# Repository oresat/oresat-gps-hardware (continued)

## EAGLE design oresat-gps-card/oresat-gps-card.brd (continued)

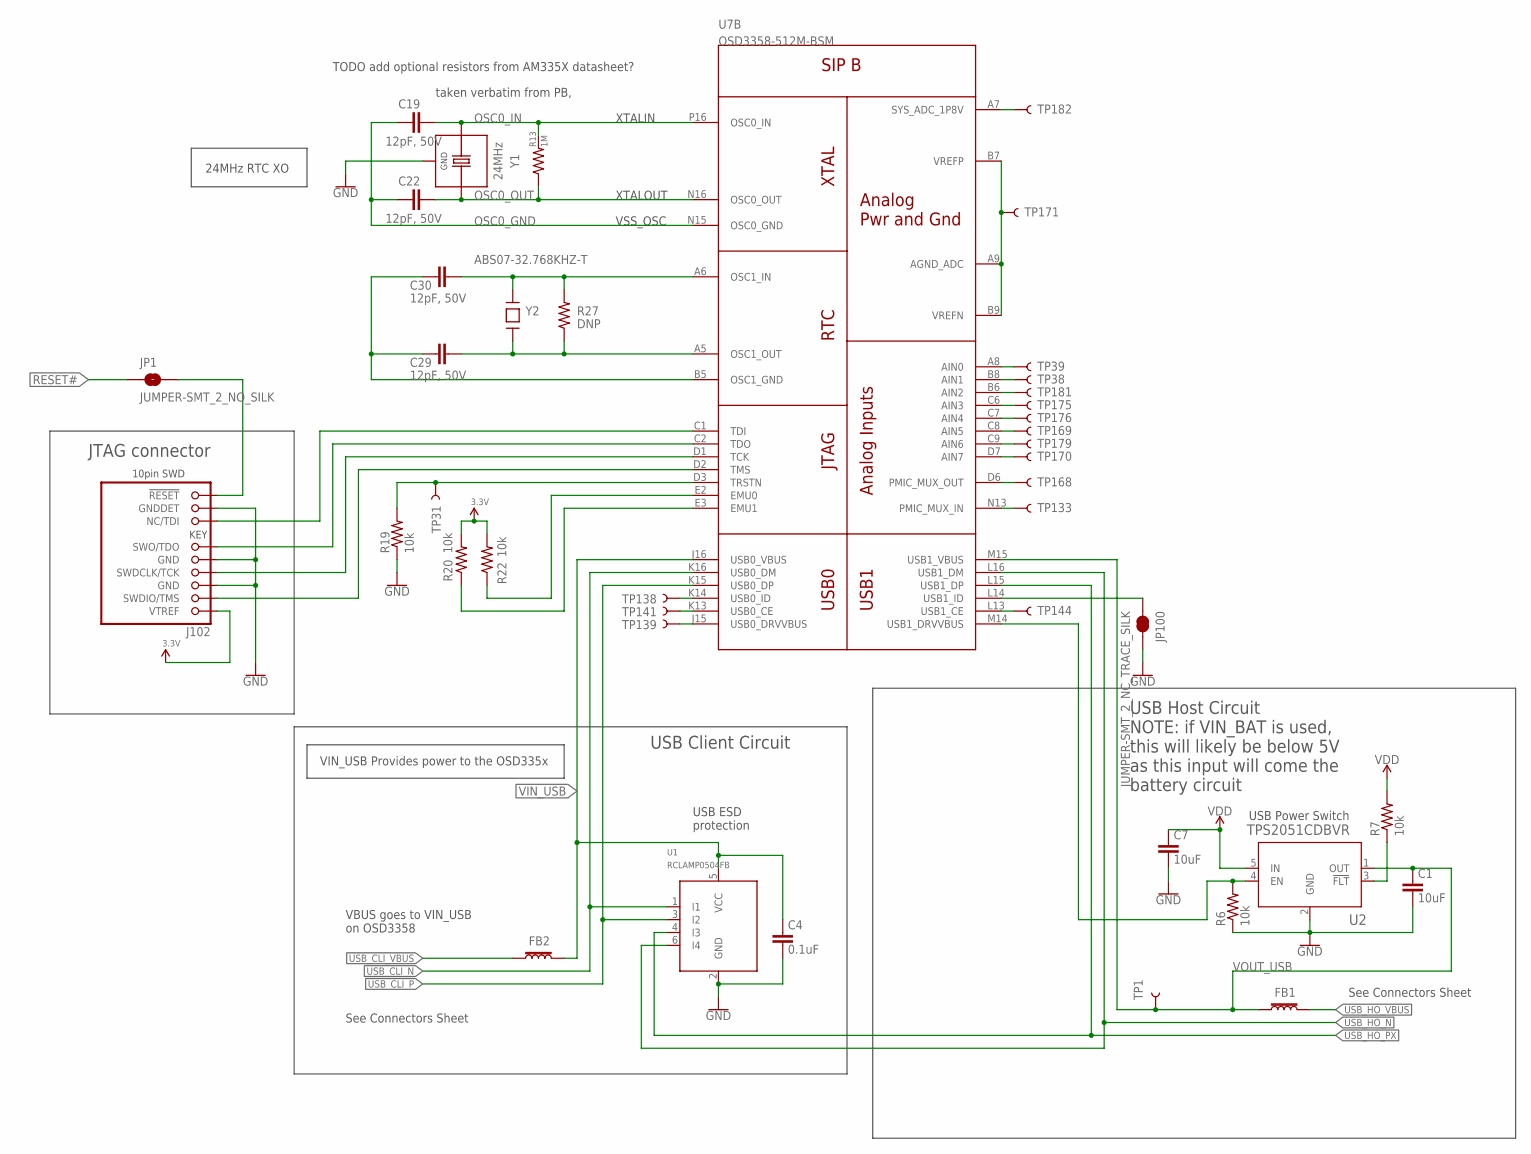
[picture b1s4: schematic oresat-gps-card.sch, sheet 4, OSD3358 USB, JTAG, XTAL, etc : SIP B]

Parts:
C1, C7: 10uF; .0805-B
C4: 0.1uF; .0603-A
C19, C22, C29, C30: 12pF, 50V; .0603-A
FB1, FB2: 30Ω/1.8A; 0603; MPN BLM18KG300JH1D
J102: FTSH-105-XX-X-DV-K; CON10_2X5_DUK_FTSH
JP1: JUMPER-SMT_2_NO_SILK; SMT-JUMPER_2_NO_SILK
JP100: JUMPER-SMT_2_NC_TRACE_SILK; SMT-JUMPER_2_NC_TRACE_SILK
R6, R7, R19, R20, R22: 10k; .0603-A
R13: 1M; .0603-A
R27: DNP; .0603-A
TP1, TP31, TP38, TP39, TP133, TP138, TP139, TP141, TP144, TP168, TP169, TP170, TP171, TP175, TP176, TP179, TP181, TP182: TEST-POINT3X4; PAD.03X.04
U1: RCLAMP0504FB; SC70-6
U2: TPS2051CDBVR; DBV5
U7: OSD3358-512M-BSM; OSD335X-BGA-256
Y1: 24MHz; 5X3.2-4SMD
Y2: ABS07-32.768KHZ-T; CRYSTAL_3.2X1.5

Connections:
3.3V: J102.1 (VTREF), R20.2, R22.2; also elsewhere on the board
GND: C1.2, C4.2, C7.2, J102.3 (GND), J102.5 (GND), J102.9 (GNDDET), JP100.2, R6.1, R19.1, U1.2 (GND), U2.2 (GND), Y1.2 (GND), Y1.4 (GND); also elsewhere on the board
unnamed: TP171.P$1, U7.A9 (AGND_ADC), U7.B7 (VREFP), U7.B9 (VREFN)
unnamed: TP170.P$1, U7.D7 (AIN7)
unnamed: TP179.P$1, U7.C9 (AIN6)
unnamed: TP169.P$1, U7.C8 (AIN5)
unnamed: TP176.P$1, U7.C7 (AIN4)
unnamed: TP175.P$1, U7.C6 (AIN3)
unnamed: TP181.P$1, U7.B6 (AIN2)
unnamed: TP38.P$1, U7.B8 (AIN1)
unnamed: TP39.P$1, U7.A8 (AIN0)
unnamed: TP141.P$1, U7.K13 (USB0_CE)
unnamed: TP139.P$1, U7.J15 (USB0_DRVVBUS)
unnamed: TP182.P$1, U7.A7 (SYS_ADC_1P8V)
unnamed: TP168.P$1, U7.D6 (PMIC_MUX_OUT)
unnamed: R20.1, U7.E3 (EMU1)
unnamed: TP144.P$1, U7.L13 (USB1_CE)
unnamed: R22.1, U7.E2 (EMU0)
unnamed: JP100.1, U7.L14 (USB1_ID)
unnamed: TP138.P$1, U7.K14 (USB0_ID)
unnamed: J102.10 (!RESET), JP1.2
unnamed: J102.6 (SWO/TDO), U7.C2 (TDO)
unnamed: J102.4 (SWDCLK/TCK), U7.D1 (TCK)
unnamed: J102.2 (SWDIO/TMS), U7.D2 (TMS)
unnamed: R6.2, U2.4 (EN), U7.M14 (USB1_DRVVBUS)
unnamed: R7.1, U2.3 (!FLT)
unnamed: J102.8 (NC/TDI), U7.C1 (TDI)
unnamed: R19.2, TP31.P$1, U7.D3 (TRSTN)
OSC0_GND: C19.1, C22.1, U7.N15 (OSC0_GND)
OSC0_IN: C19.2, R13.2, U7.P16 (OSC0_IN), Y1.1 (X1)
OSC0_OUT: C22.2, R13.1, U7.N16 (OSC0_OUT), Y1.3 (X2)
OSC1_GND1: C29.2, C30.2, U7.B5 (OSC1_GND)
OSC1_IN1: C30.1, R27.2, U7.A6 (OSC1_IN), Y2.P$2
OSC1_OUT1: C29.1, R27.1, U7.A5 (OSC1_OUT), Y2.P$1
PMIC_MUX_IN: TP133.P$1, U7.N13 (PMIC_MUX_IN)
RESET#: JP1.1; also elsewhere on the board
USB_CLI_N: U1.1 (I1), U7.K16 (USB0_DM); also elsewhere on the board
USB_CLI_P: U1.3 (I2), U7.K15 (USB0_DP); also elsewhere on the board
USB_CLI_VBUS: FB2.1; also elsewhere on the board
USB_HO_N: U1.6 (I4), U7.L16 (USB1_DM); also elsewhere on the board
USB_HO_PX: U1.4 (I3), U7.L15 (USB1_DP); also elsewhere on the board
USB_HO_VBUS: FB1.2; also elsewhere on the board
VDD: C7.1, R7.2, U2.5 (IN); also elsewhere on the board
VIN_USB: C4.1, FB2.2, U1.5 (VCC), U7.J16 (USB0_VBUS); also elsewhere on the board
VOUT_USB: C1.1, FB1.1, TP1.P$1, U2.1 (OUT), U7.M15 (USB1_VBUS)

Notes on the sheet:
taken verbatim from PB,
VBUS goes to VIN_USB on OSD3358
USB ESD protection
USB Host Circuit NOTE: if VIN_BAT is used, this will likely be below 5V as this input will come the battery circuit
USB Power Switch
JTAG connector
USB Client Circuit
24MHz RTC XO
See Connectors Sheet
TODO add optional resistors from AM335X datasheet?
XTALIN
XTALOUT
VSS_OSC
VIN_USB Provides power to the OSD335x

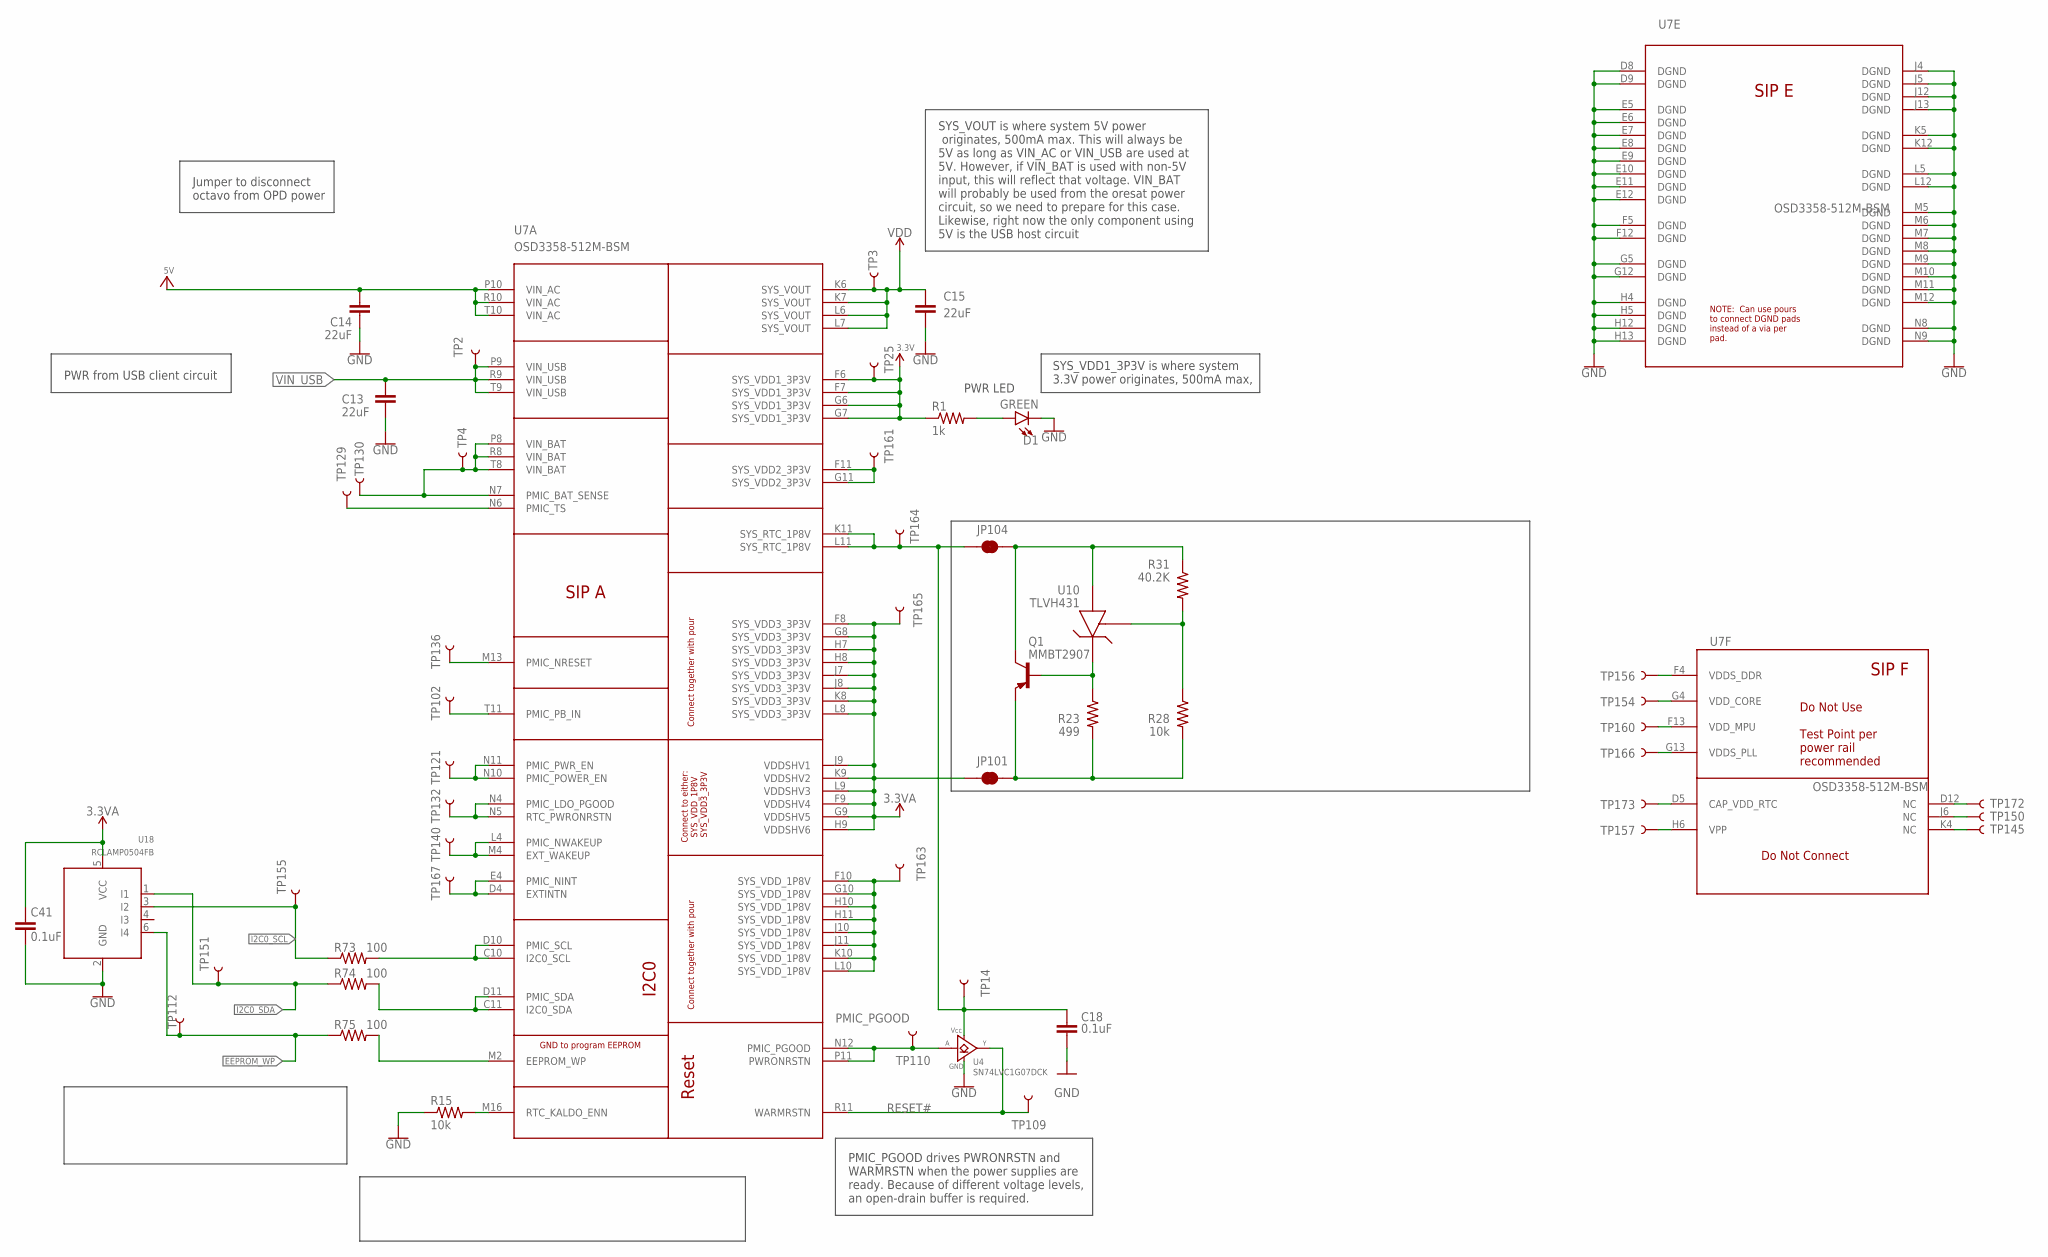
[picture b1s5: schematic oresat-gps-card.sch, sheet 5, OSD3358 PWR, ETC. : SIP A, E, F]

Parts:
C13, C14, C15: 22uF; C1210
C18, C41: 0.1uF; .0603-A
D1: GREEN; LED-0603
JP101, JP104: JUMPER-SMT_2_NC_TRACE_SILK; SMT-JUMPER_2_NC_TRACE_SILK
Q1: MMBT2907; SOT23-BEC
R1: 1k; .0603-A
R15, R28: 10k; .0603-A
R23: 499; .0603-A
R31: 40.2K; .0603-A
R73, R74, R75: 100; .0603-A
TP2, TP3, TP4, TP14, TP25, TP102, TP109, TP110, TP112, TP121, TP129, TP130, TP132, TP136, TP140, TP145, TP150, TP151, TP154, TP155, TP156, TP157, TP160, TP161, TP163, TP164, TP165, TP166, TP167, TP172, TP173: TEST-POINT3X4; PAD.03X.04
U4: SN74LVC1G07DCK; C70(TI-DCK)
U7: OSD3358-512M-BSM; OSD335X-BGA-256
U10: TLVH431; SOT23-3
U18: RCLAMP0504FB; SC70-6

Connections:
3.3V: R1.1, TP25.P$1, U7.F6 (SYS_VDD1_3P3V), U7.F7 (SYS_VDD1_3P3V), U7.G6 (SYS_VDD1_3P3V), U7.G7 (SYS_VDD1_3P3V); also elsewhere on the board
3.3VA: C41.1, JP101.1, TP165.P$1, U7.F8 (SYS_VDD3_3P3V), U7.F9 (VDDSHV4), U7.G8 (SYS_VDD3_3P3V), U7.G9 (VDDSHV5), U7.H7 (SYS_VDD3_3P3V), U7.H8 (SYS_VDD3_3P3V), U7.H9 (VDDSHV6), U7.J7 (SYS_VDD3_3P3V), U7.J8 (SYS_VDD3_3P3V), U7.J9 (VDDSHV1), U7.K8 (SYS_VDD3_3P3V), U7.K9 (VDDSHV2), U7.L8 (SYS_VDD3_3P3V), U7.L9 (VDDSHV3), U18.5 (VCC)
5V: C14.1, U7.P10 (VIN_AC), U7.R10 (VIN_AC), U7.T10 (VIN_AC); also elsewhere on the board
EEPROM_WP: R75.1, TP112.P$1, U18.6 (I4); also elsewhere on the board
GND: C13.2, C14.2, C15.2, C18.2, C41.2, D1.C, R15.1, U4.3 (GND), U7.D8 (DGND), U7.D9 (DGND), U7.E5 (DGND), U7.E6 (DGND), U7.E7 (DGND), U7.E8 (DGND), U7.E9 (DGND), U7.E10 (DGND), U7.E11 (DGND), U7.E12 (DGND), U7.F5 (DGND), U7.F12 (DGND), U7.G5 (DGND), U7.G12 (DGND), U7.H4 (DGND), U7.H5 (DGND), U7.H12 (DGND), U7.H13 (DGND), U7.J4 (DGND), U7.J5 (DGND), U7.J12 (DGND), U7.J13 (DGND), U7.K5 (DGND), U7.K12 (DGND), U7.L5 (DGND), U7.L12 (DGND), U7.M5 (DGND), U7.M6 (DGND), U7.M7 (DGND), U7.M8 (DGND), U7.M9 (DGND), U7.M10 (DGND), U7.M11 (DGND), U7.M12 (DGND), U7.N8 (DGND), U7.N9 (DGND), U18.2 (GND); also elsewhere on the board
I2C0_SCL: R73.1, TP155.P$1, U18.3 (I2); also elsewhere on the board
I2C0_SDA: R74.1, TP151.P$1, U18.1 (I1); also elsewhere on the board
unnamed: JP101.2, Q1.E, R23.2, R28.2
unnamed: R28.1, R31.2, U10.1 (REF)
unnamed: Q1.B, R23.1, U10.2 (CATHODE)
unnamed: TP172.P$1, U7.D12 (NC)
unnamed: TP150.P$1, U7.J6 (NC)
unnamed: TP145.P$1, U7.K4 (NC)
unnamed: TP157.P$1, U7.H6 (VPP)
unnamed: TP173.P$1, U7.D5 (CAP_VDD_RTC)
unnamed: TP166.P$1, U7.G13 (VDDS_PLL)
unnamed: TP160.P$1, U7.F13 (VDD_MPU)
unnamed: TP154.P$1, U7.G4 (VDD_CORE)
unnamed: TP156.P$1, U7.F4 (VDDS_DDR)
unnamed: D1.A, R1.2
unnamed: R74.2, U7.C11 (I2C0_SDA), U7.D11 (PMIC_SDA)
unnamed: R75.2, U7.M2 (EEPROM_WP)
unnamed: R73.2, U7.C10 (I2C0_SCL), U7.D10 (PMIC_SCL)
unnamed: C18.1, JP104.1, TP14.P$1, TP164.P$1, U4.5 (VCC), U7.K11 (SYS_RTC_1P8V), U7.L11 (SYS_RTC_1P8V)
unnamed: TP4.P$1, TP130.P$1, U7.N7 (PMIC_BAT_SENSE), U7.P8 (VIN_BAT), U7.R8 (VIN_BAT), U7.T8 (VIN_BAT)
unnamed: TP129.P$1, U7.N6 (PMIC_TS)
unnamed: TP161.P$1, U7.F11 (SYS_VDD2_3P3V), U7.G11 (SYS_VDD2_3P3V)
unnamed: JP104.2, Q1.C, R31.1, U10.3 (ANODE)
unnamed: TP163.P$1, U7.F10 (SYS_VDD_1P8V), U7.G10 (SYS_VDD_1P8V), U7.H10 (SYS_VDD_1P8V), U7.H11 (SYS_VDD_1P8V), U7.J10 (SYS_VDD_1P8V), U7.J11 (SYS_VDD_1P8V), U7.K10 (SYS_VDD_1P8V), U7.L10 (SYS_VDD_1P8V)
unnamed: TP167.P$1, U7.D4 (EXTINTN), U7.E4 (PMIC_NINT)
unnamed: TP140.P$1, U7.L4 (PMIC_NWAKEUP), U7.M4 (EXT_WAKEUP)
unnamed: TP132.P$1, U7.N4 (PMIC_LDO_PGOOD), U7.N5 (RTC_PWRONRSTN)
unnamed: TP121.P$1, U7.N10 (PMIC_POWER_EN), U7.N11 (PMIC_PWR_EN)
unnamed: TP102.P$1, U7.T11 (PMIC_PB_IN)
unnamed: TP136.P$1, U7.M13 (PMIC_NRESET)
unnamed: R15.2, U7.M16 (RTC_KALDO_ENN)
PMIC_PGOOD: TP110.P$1, U4.2 (A), U7.N12 (PMIC_PGOOD), U7.P11 (PWRONRSTN)
RESET#: TP109.P$1, U4.4 (Y), U7.R11 (WARMRSTN); also elsewhere on the board
VDD: C15.1, TP3.P$1, U7.K6 (SYS_VOUT), U7.K7 (SYS_VOUT), U7.L6 (SYS_VOUT), U7.L7 (SYS_VOUT); also elsewhere on the board
VIN_USB: C13.1, TP2.P$1, U7.P9 (VIN_USB), U7.R9 (VIN_USB), U7.T9 (VIN_USB); also elsewhere on the board

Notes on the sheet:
SYS_VOUT is where system 5V power originates, 500mA max. This will always be 5V as long as VIN_AC or VIN_USB are used at 5V. However, if VIN_BAT is used with non-5V input, this will reflect that voltage. VIN_BAT will probably be used from the oresat power circuit, so we need to prepare for this cas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
SYS_VDD1_3P3V is where system 3.3V power originates, 500mA max,
PWR LED
PMIC_PGOOD drives PWRONRSTN and WARMRSTN when the power supplies are ready. Because of different voltage levels, an open-drain buffer is required.
PWR from USB client circuit
Jumper to disconnect octavo from OPD power

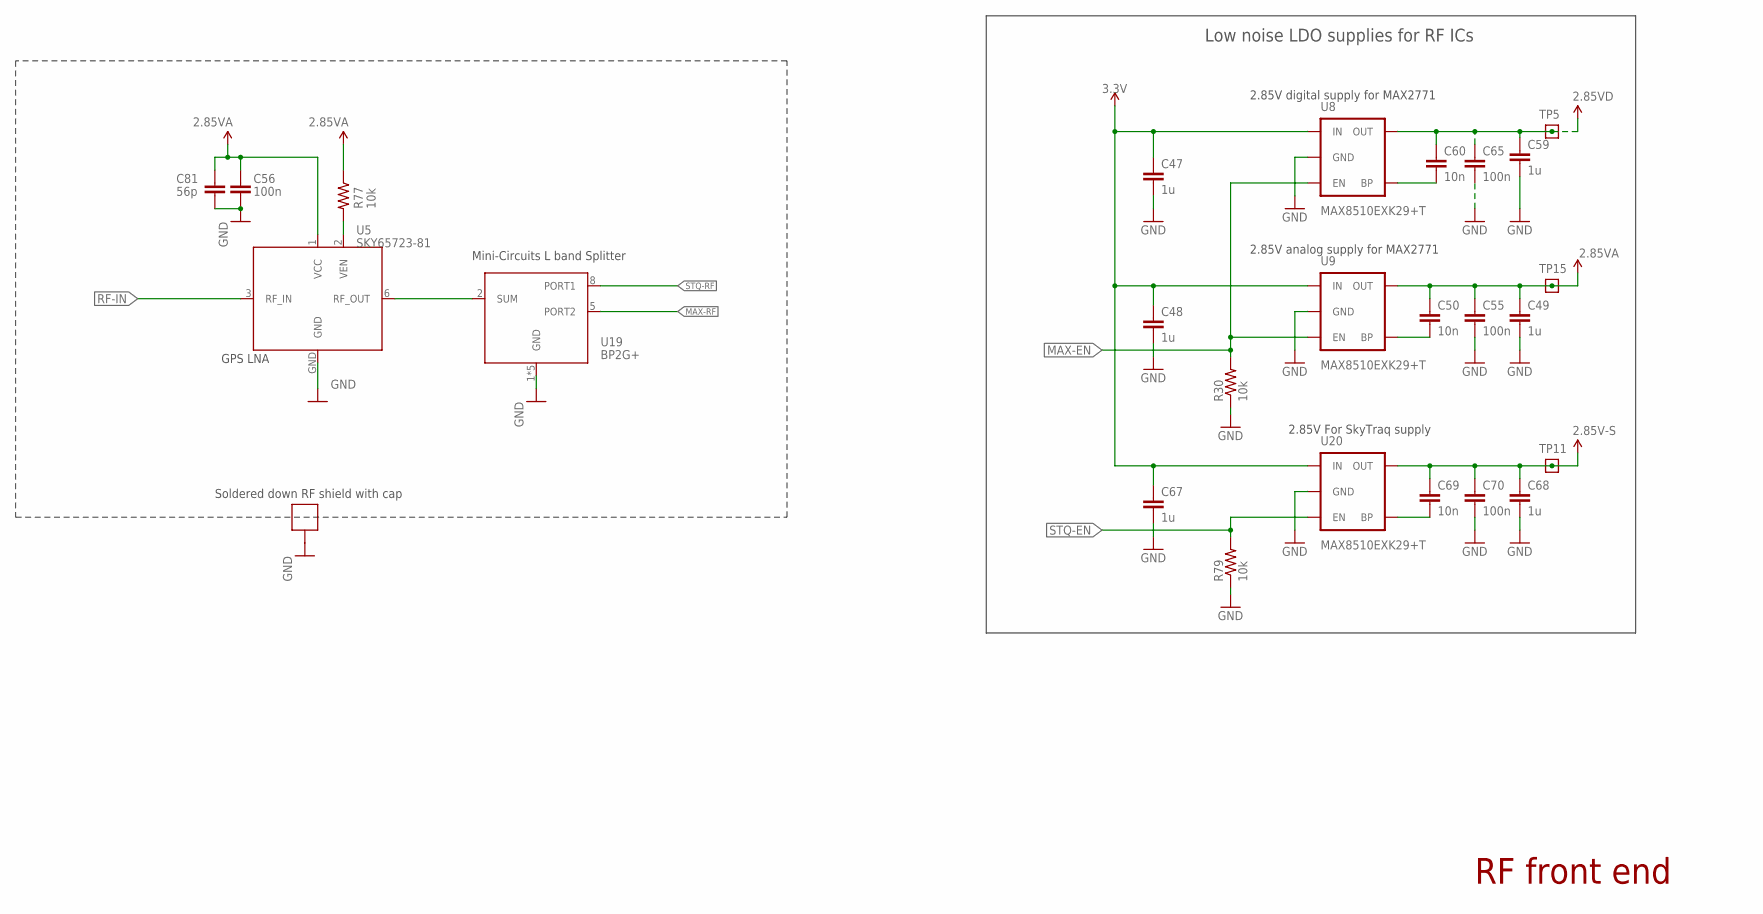
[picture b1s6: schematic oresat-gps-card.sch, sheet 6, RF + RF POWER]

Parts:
C47, C48, C49, C59, C67, C68: 1u; .0603-B-NOSILK
C50, C60, C69: 10n; .0603-B-NOSILK
C55, C56, C65, C70: 100n; .0603-B-NOSILK
C81: 56p; .0402-C-NOSILK
R30, R79: 10k; .0603-B-NOSILK
R77: 10k; 0402-C-NOSILK@1
SH1: BMI-S-202-SHIELD; BMI-S-202; MPN BMI-S-202-C
TP5, TP11, TP15: TEST-POINT15MIL-TEST-POINT; 15MIL-TEST-POINT
U5: SKY65723-81; MPN SKY65723-81
U8, U9, U20: MAX8510EXK29+T; SC70; MPN MAX8510EXK29+T
U19: BP2G+; MINICIRCUITS

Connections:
2.85V-S: C68.1, C69.1, C70.1, TP11.P$1, U20.5 (OUT); also elsewhere on the board
2.85VA: C49.1, C50.1, C55.1, C56.1, C81.1, R77.1, TP15.P$1, U5.1 (VCC), U9.5 (OUT); also elsewhere on the board
2.85VD: C59.1, C60.1, C65.1, TP5.P$1, U8.5 (OUT); also elsewhere on the board
3.3V: C47.1, C48.1, C67.1, U8.1 (IN), U9.1 (IN), U20.1 (IN); also elsewhere on the board
GND: C47.2, C48.2, C49.2, C55.2, C56.2, C59.2, C65.2, C67.2, C68.2, C70.2, C81.2, R30.1, R79.1, SH1.P$1, SH1.P$2, SH1.P$3, SH1.P$4, SH1.P$5, SH1.P$6, SH1.P$7, SH1.P$8, SH1.P$9, SH1.P$10, SH1.P$11, SH1.P$12, U5.GND, U8.2 (GND), U9.2 (GND), U19.1 (GND), U19.3 (GND), U19.4 (GND), U19.6 (GND), U19.7 (GND), U20.2 (GND); also elsewhere on the board
MAX-EN: R30.2, U8.3 (EN), U9.3 (EN); also elsewhere on the board
MAX-RF: U19.5 (PORT2); also elsewhere on the board
unnamed: U5.6 (RF_OUT), U19.2 (SUM)
unnamed: R77.2, U5.2 (VEN)
unnamed: C50.2, U9.4 (BP)
unnamed: C60.2, U8.4 (BP)
unnamed: C69.2, U20.4 (BP)
RF-IN: U5.3 (RF_IN); also elsewhere on the board
STQ-EN: R79.2, U20.3 (EN); also elsewhere on the board
STQ-RF: U19.8 (PORT1); also elsewhere on the board

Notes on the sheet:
Soldered down RF shield with cap
Mini-Circuits L band Splitter
GPS LNA
RF front end
2.85V digital supply for MAX2771
2.85V For SkyTraq supply
2.85V analog supply for MAX2771
Low noise LDO supplies for RF ICs

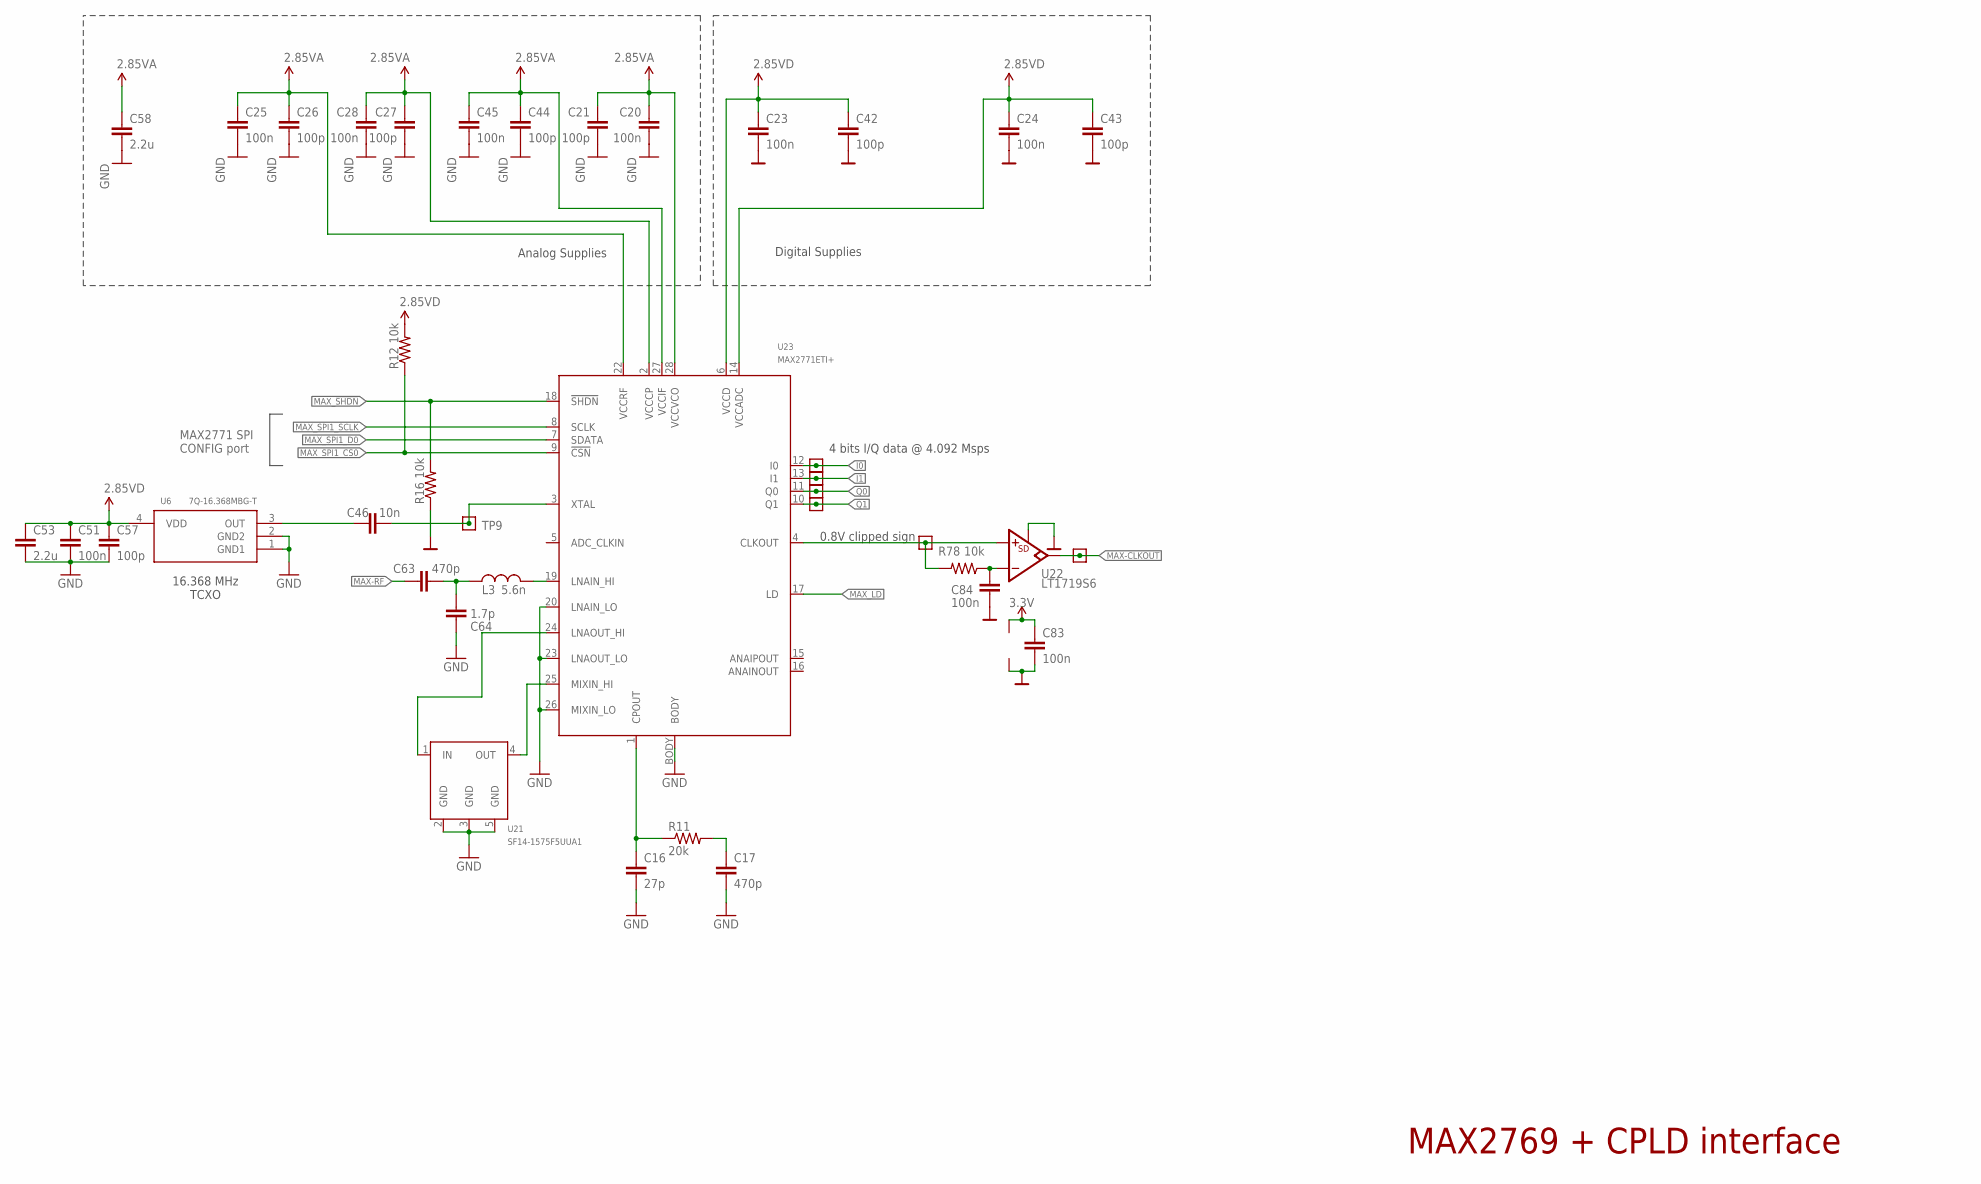
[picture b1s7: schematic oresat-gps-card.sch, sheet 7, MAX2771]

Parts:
C16: 27p; .0603-B-NOSILK
C17: 470p; .0603-B-NOSILK
C20, C23, C24, C25, C28, C45, C51, C83, C84: 100n; .0603-B-NOSILK
C21, C26, C27, C42, C43, C44, C57: 100p; .0603-B-NOSILK
C46: 10n; .0603-B-NOSILK
C53, C58: 2.2u; .0603-B-NOSILK
C63: 470p; .0402-B-NOSILK
C64: 1.7p; .0402-B-NOSILK
L3: 5.6n; .0402-B-NOSILK
R11: 20k; .0603-B-NOSILK
R12, R16, R78: 10k; .0603-B-NOSILK
TP9: TEST-POINT15MIL-TEST-POINT; 15MIL-TEST-POINT
TP20, TP21, TP33, TP34, TP71, TP72: TEST-POINT-LARGE-SQUARE; 1X01
U6: 7Q-16.368MBG-T; TCX_7Q
U21: SF14-1575F5UUA1; SAW_1.4X1.1; MPN SF14-1575F5UUA1
U22: LT1719S6; SOT23-6
U23: MAX2771ETI+; 90-0023; MPN MAX2771ETI+

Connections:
2.85VA: C20.1, C21.1, C25.1, C26.1, C27.1, C28.1, C44.1, C45.1, C58.1, U23.2 (VCCCP), U23.22 (VCCRF), U23.27 (VCCIF), U23.28 (VCCVCO); also elsewhere on the board
2.85VD: C23.1, C24.1, C42.1, C43.1, C51.1, C53.1, C57.1, R12.2, U6.4 (VDD), U23.6 (VCCD), U23.14 (VCCADC); also elsewhere on the board
3.3V: C83.1, U22.4 (V+); also elsewhere on the board
CPOUT: C16.1, R11.1, U23.1 (CPOUT)
GND: C16.2, C17.2, C20.2, C21.2, C23.2, C24.2, C25.2, C26.2, C27.2, C28.2, C42.2, C43.2, C44.2, C45.2, C51.2, C53.2, C57.2, C58.2, C64.1, C83.2, C84.2, R16.1, U6.1 (GND1), U6.2 (GND2), U21.2 (GND), U21.3 (GND), U21.5 (GND), U22.2 (V-), U22.6 (SD), U23.20 (LNAIN_LO), U23.23 (LNAOUT_LO), U23.26 (MIXIN_LO), U23.BODY; also elsewhere on the board
I0: TP20.1, U23.12 (I0); also elsewhere on the board
I1: TP21.1, U23.13 (I1); also elsewhere on the board
LNAOUT: U21.1 (IN), U23.24 (LNAOUT_HI)
MAX-CLKOUT: TP72.1, U22.5 (OUT); also elsewhere on the board
MAX-RF: C63.1; also elsewhere on the board
MAX_!SHDN: R16.2, U23.18 (!SHDN); also elsewhere on the board
MAX_CLK_OUT: R78.2, TP71.1, U22.3 (+IN), U23.4 (CLKOUT)
MAX_LD: U23.17 (LD); also elsewhere on the board
MAX_SPI1_CS0: R12.1, U23.9 (!CSN); also elsewhere on the board
MAX_SPI1_D0: U23.7 (SDATA); also elsewhere on the board
MAX_SPI1_SCLK: U23.8 (SCLK); also elsewhere on the board
MIXIN: U21.4 (OUT), U23.25 (MIXIN_HI)
unnamed: C17.1, R11.2
unnamed: C46.1, U6.3 (OUT)
unnamed: C84.1, R78.1, U22.1 (-IN)
unnamed: C63.2, C64.2, L3.1
unnamed: L3.2, U23.19 (LNAIN_HI)
Q0: TP33.1, U23.11 (Q0); also elsewhere on the board
Q1: TP34.1, U23.10 (Q1); also elsewhere on the board
XTAL: C46.2, TP9.P$1, U23.3 (XTAL)

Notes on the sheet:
Digital Supplies
Analog Supplies
MAX2771 SPI CONFIG port
4 bits I/Q data @ 4.092 Msps
16.368 MHz TCXO
0.8V clipped sign
MAX2769 + CPLD interface

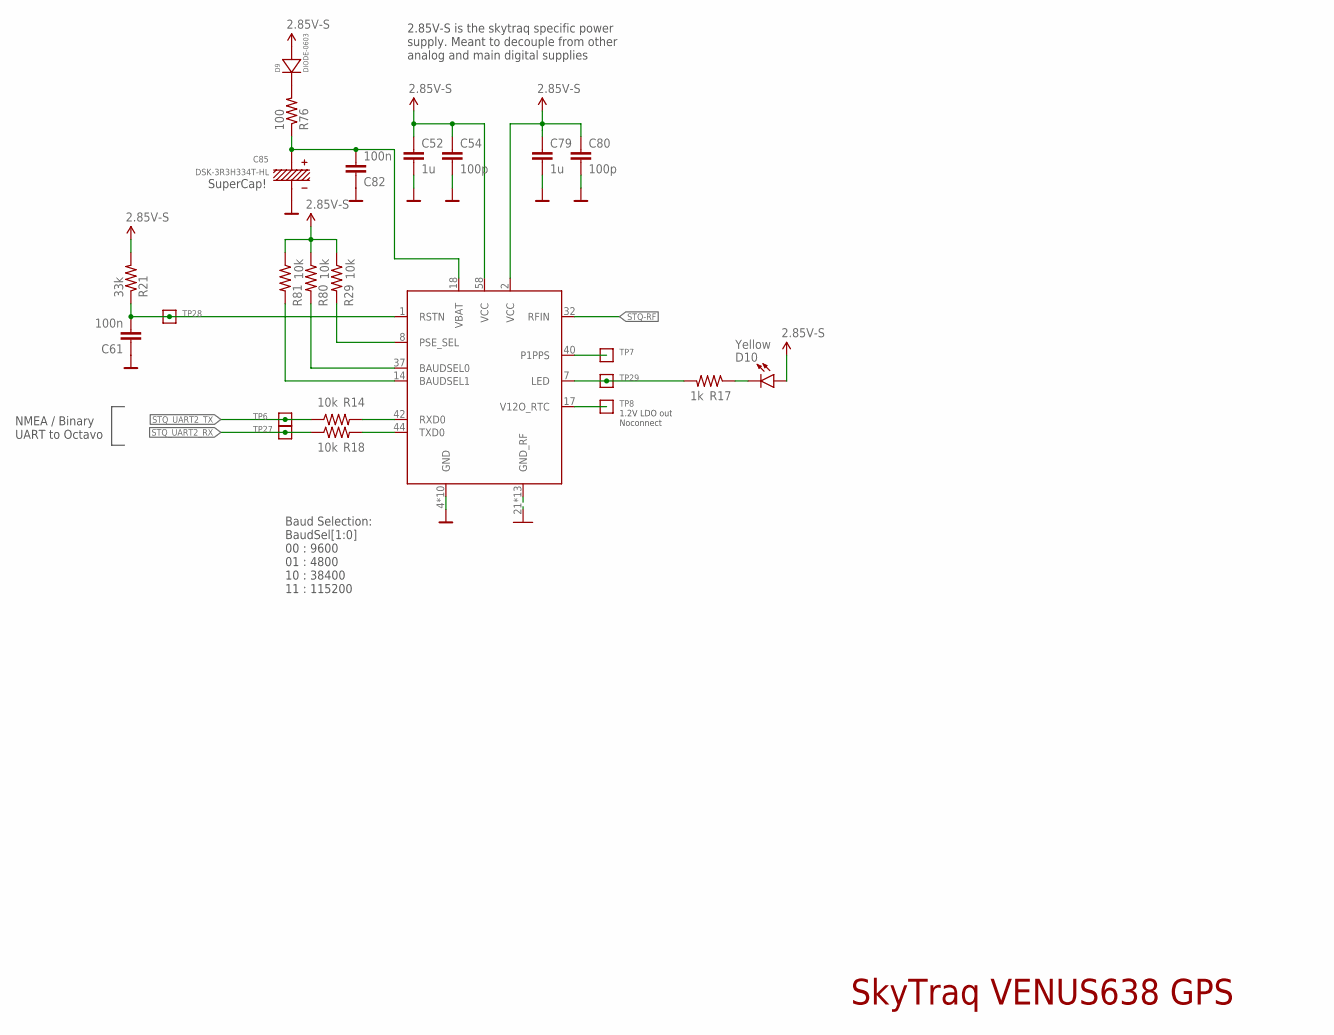
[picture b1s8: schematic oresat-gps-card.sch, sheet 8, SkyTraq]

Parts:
C52, C79: 1u; .0603-B-NOSILK
C54, C80: 100p; .0603-B-NOSILK
C61, C82: 100n; .0603-B-NOSILK
C85: DSK-3R3H334T-HL; CAP-ELNA-DS-SERIES
D9: DIODE-0603; 0603-B-NOSILK-DIODE
D10: Yellow; LED-0603
R14, R18, R29, R80, R81: 10k; .0603-B-NOSILK
R17: 1k; .0603-B-NOSILK
R21: 33k; .0603-B-NOSILK
R76: 100; .0603-B-NOSILK
TP6, TP7, TP8, TP27, TP28, TP29: TEST-POINT15MIL-TEST-POINT; 15MIL-TEST-POINT
U24: VENUS838LPX-L; VENUS838LPX

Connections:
2.85V-S: C52.1, C54.1, C79.1, C80.1, D9.ANODE, D10.A, R21.2, R29.1, R80.1, R81.1, U24.2 (VCC), U24.58 (VCC); also elsewhere on the board
GND: C52.2, C54.2, C61.1, C79.2, C80.2, C82.1, C85.-, U24.4 (GND), U24.5 (GND), U24.6 (GND), U24.10 (GND), U24.11 (GND), U24.15 (GND), U24.19 (GND), U24.21 (GND_RF), U24.22 (GND_RF), U24.24 (GND_RF), U24.25 (GND_RF), U24.27 (GND_RF), U24.28 (GND_RF), U24.29 (GND_RF), U24.31 (GND_RF), U24.33 (GND_RF), U24.49 (GND), U24.60 (GND), U24.61 (GND_RF), U24.62 (GND_RF), U24.64 (GND), U24.65 (GND_RF), U24.69 (GND_RF); also elsewhere on the board
LED: R17.2, TP29.P$1, U24.7 (LED)
unnamed: R80.2, U24.37 (BAUDSEL0)
unnamed: R81.2, U24.14 (BAUDSEL1)
unnamed: R14.2, U24.42 (RXD0)
unnamed: R18.2, U24.44 (TXD0)
unnamed: D10.C, R17.1
unnamed: D9.CATHODE, R76.2
unnamed: TP8.P$1, U24.17 (V12O_RTC)
unnamed: R29.2, U24.8 (PSE_SEL)
STQ-!RST: C61.2, R21.1, TP28.P$1, U24.1 (RSTN)
STQ-PPS: TP7.P$1, U24.40 (P1PPS)
STQ-RF: U24.32 (RFIN); also elsewhere on the board
STQ-VBAT: C82.2, C85.+, R76.1, U24.18 (VBAT)
STQ_UART2_RX: R18.1, TP27.P$1; also elsewhere on the board
STQ_UART2_TX: R14.1, TP6.P$1; also elsewhere on the board

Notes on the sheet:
1.2V LDO out Noconnect
SuperCap!
2.85V-S is the skytraq specific power supply. Meant to decouple from other analog and main digital supplies
SkyTraq VENUS638 GPS
NMEA / Binary UART to Octavo
Baud Selection: BaudSel[1:0] 00 : 9600 01 : 4800 10 : 38400 11 : 115200

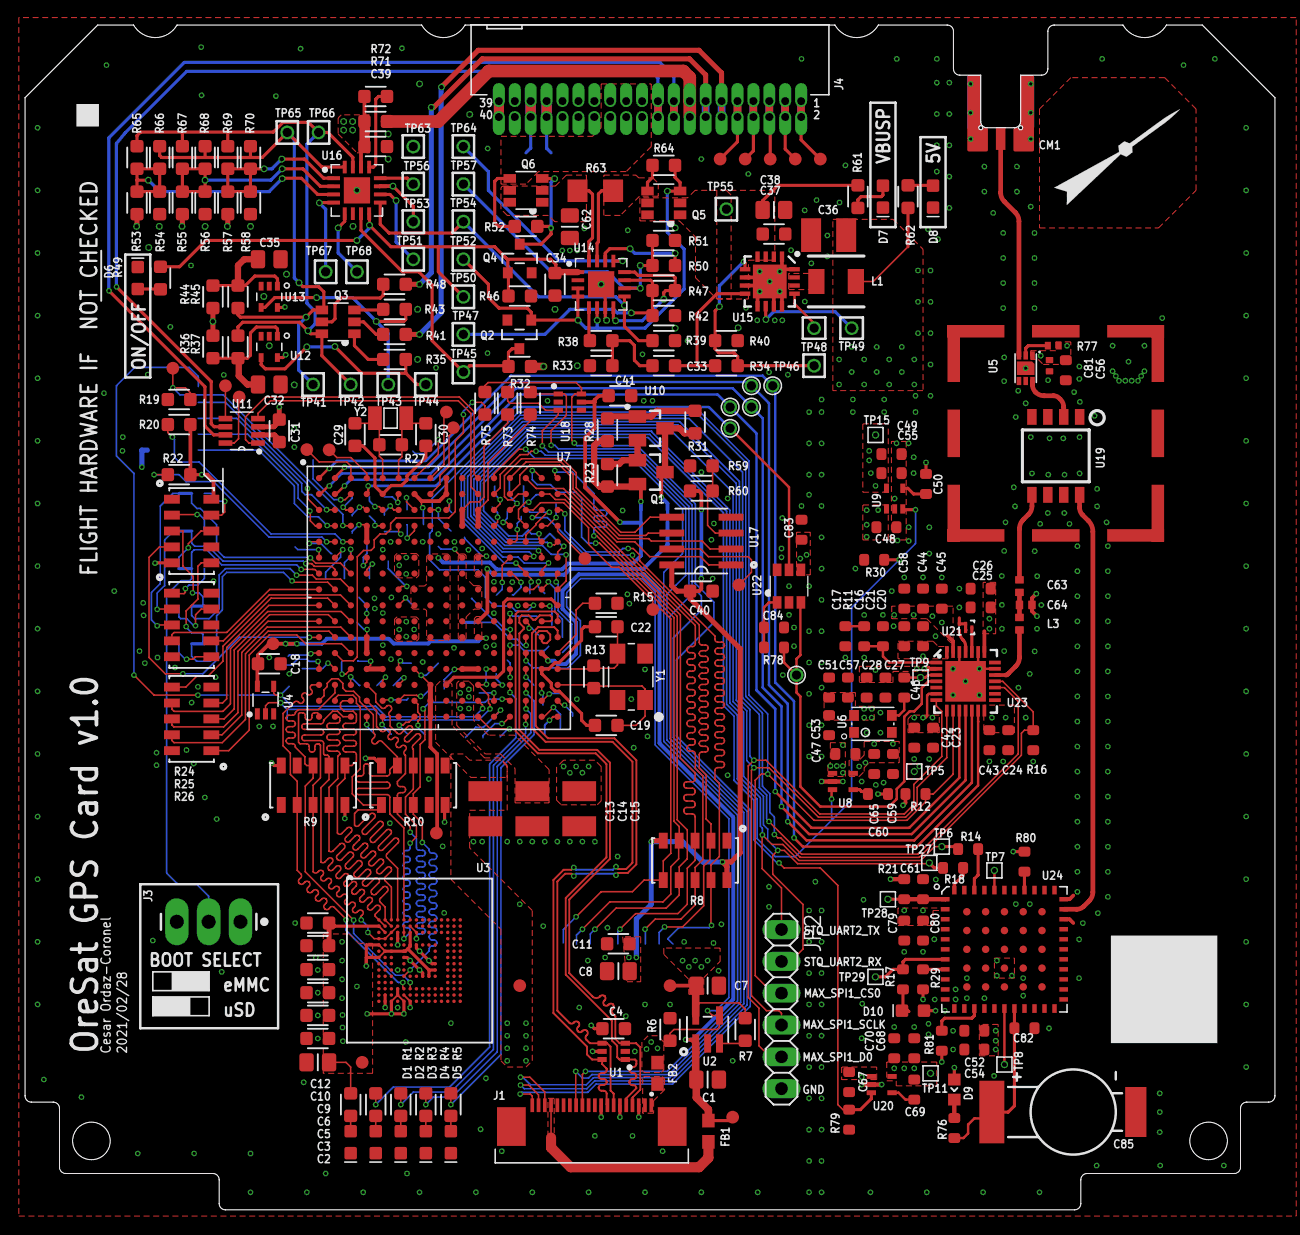
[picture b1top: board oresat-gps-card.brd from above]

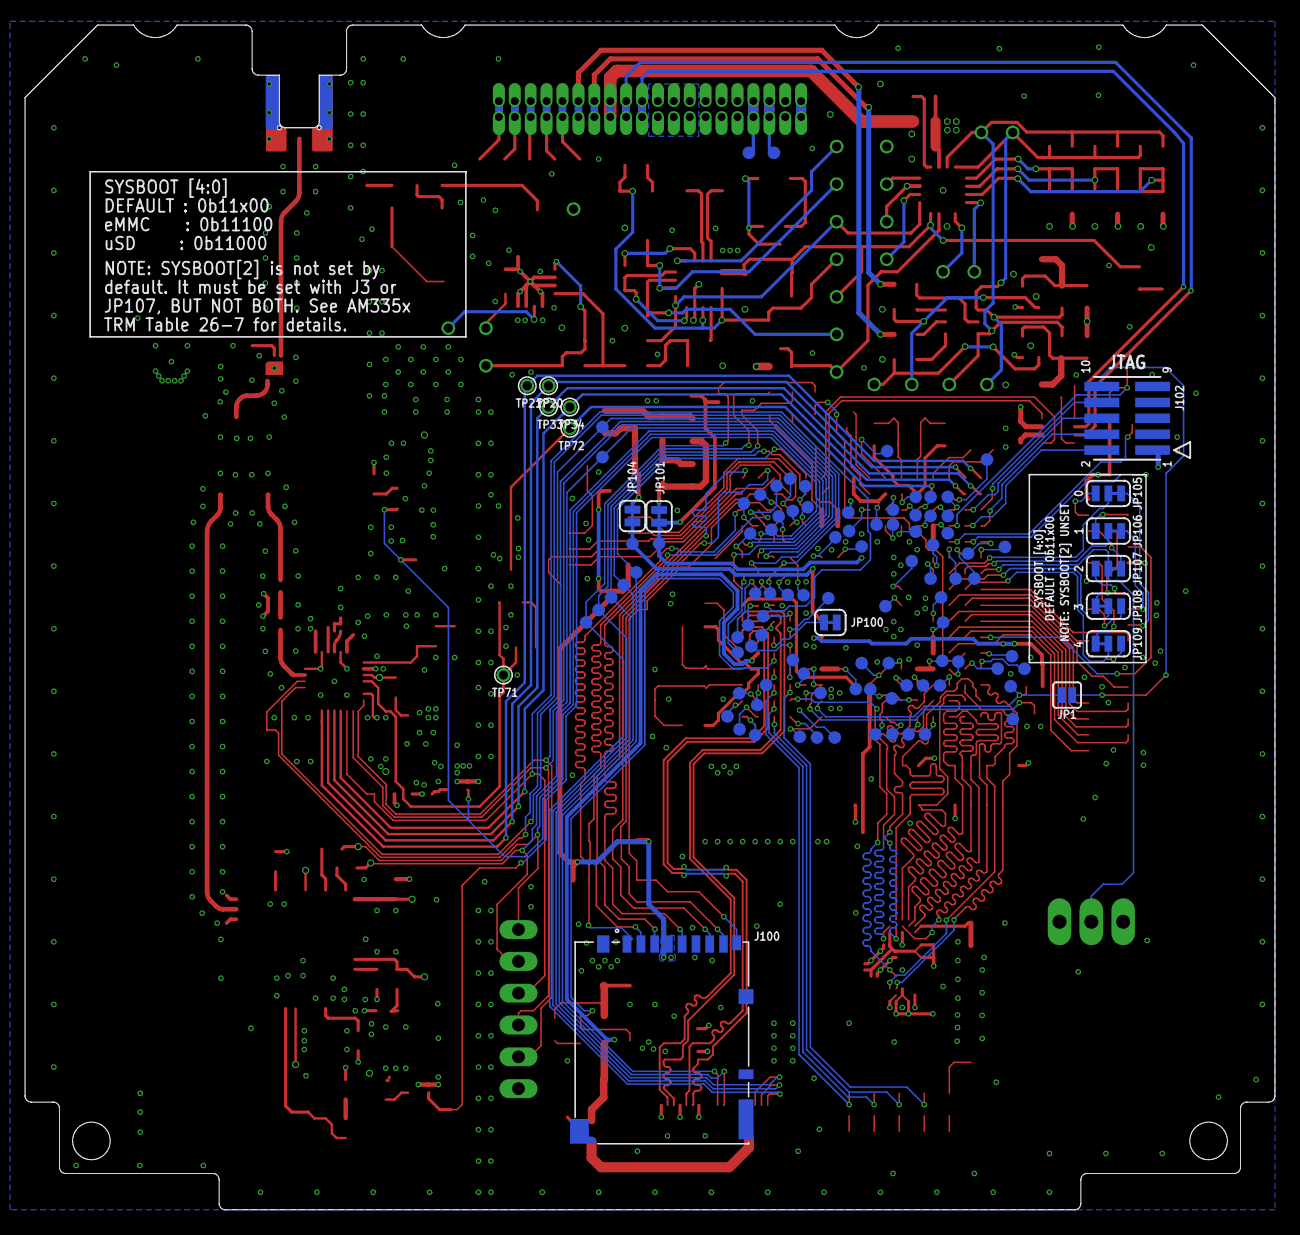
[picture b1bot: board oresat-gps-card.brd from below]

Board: 4 copper layers, 99.8 x 94.6 mm, 373 parts (101 on the bottom side), 291 nets.

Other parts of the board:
U$3: PSAS_LOGO_10X10
U$4: FLIGHTMARKER_OLD_BOARDS

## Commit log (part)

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2019-03-20 Moving the GPS USB front end board from PSAS repo.
2019-07-18 Fix 3.3V LDO inhibit polarity.
2019-07-18 Fix footprint for MAX 8510 (two places).
2019-07-20 Change out micro-usb connector to one with thru holes.
2019-07-20 Change out SMA connector for thru-hole version.
2019-07-22 Add back mounting holes, rev. front silk.
2019-07-24 Minor cleanup.
2019-07-26 Update to MAX2771. Changes to decoupling caps, Remove ANTFLAG, IDLE signals. Add explicit antenna bias. New matching network for LNA input. Remove bypass for SAW filter.
2019-07-27 Add some footprints, annotate new parts, generate netlist, EDR check.
2019-07-27 Intermediate routing.
2019-07-28 Changed 2.2uF to 10uF. Completed routing. Added via fencing and footprint vias.
2019-07-28 Final cleanup before submit to OSHPARK.
2019-08-02 Fix value display on EEPROM. Consolidate some part values.
2019-08-20 "auto-generated from update_repos.py"
2019-09-15 as sent to OSHPARK
2019-10-30 Add more decoupling caps to 2232H.
2019-10-30 Run DRC, generate and import netlist w/ new caps.
2019-11-01 Partially laid out; ready to move some parts.
2019-11-01 Moved optional Maxim clk fix circuit to FTDI side.
2019-11-01 Now passes DRC.
2019-11-01 Plotted gerbers. Fixed crystal load caps, added LED, added stitching.
2019-11-02 Change SMA footprint, add SAW filter, extend header pins.
2019-11-03 Add signals to header.
2019-11-13 Add LED P/N. Process BOM prior to order.
2019-11-17 Add in Microsemi A3P250 development board. Layout almost completed.
2019-11-17 Routed, fixed labels, added test points.
2019-12-01 Add solder paste layer.
2020-09-27 Added cobbled together star tracker + rocket SDR GPS receiver
2021-01-24 GPS card has been mostly layed out. Still missing a few things, but nothing major.
2021-01-24 Added some polygons to the power plane
2021-02-01 Finished laying out Venus receiver. Fixed issue with GND and AGND planes. Added vias, and restrict lines to separate digital and RF ground planes. Added enable lines to Max and Venus receivers. Updat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
2021-02-01 Fixed a note in the schematic
2021-02-03 Updated boot circuitry. Cleaned up names layer.
2021-02-06 Moved some silk screen items out of the way of pads
2021-02-08 Fixed design review things: made net names more clear, removed solder mask from top of RF traces, opened up space around octavo 3.3v pads, moved digital LDO for the max chip, added pin header and thr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
2021-02-20 Fixed 3.3VA rail for I2C protection chip.
2021-02-28 Added attributes to some parts, and changed internal cutout polygons to 0.1 width instead of 0 width.
2021-03-01 Updated oscillator capacitor values and added BOM
2021-03-08 OK'd ERC errors.
2021-03-25 Updated BOM after stuffing v1.0: added shield, a 1uF was accidentally marked as 0.1 uF, and since the supercap is DNP, stuff the diode and resistor associated with 0 ohm 0603 resistors.
2022-08-02 Updated gitignore for kicad files
2022-08-02 Moved old EAGLE files to separate folder
2022-10-02 GPS card is in KiCad now
2022-10-02 Added separation between digital and RF gnd
2023-01-22 GPS card design review changes and issue fixes
2023-01-22 Changed GPS card schematic sheet naming convention
2023-01-22 Updated schematic sheet links to match new naming
2023-01-22 Fixed date on GPS card
2023-01-22 Quick GPS card design review changes
2023-07-20 Updated GPS card with changes from C3 and notes. Fixed library issues
2023-08-31 Updated GPS card
2024-01-02 Update RF path for sunstone board run, and connected VPD diodes
2024-01-02 Updated library paths for GPS card schematic
2024-01-02 Cleaned up ERC and DRC errors on GPS card
2024-01-02 Version 1.1 of the GPS card, now in KiCAD. Updated .gitignore file, too.
2024-01-18 Added license file. Also small changd to DRU and power planes.
2024-01-18 3D model of eMMC
2024-05-25 Updated KiCAD 8, updated schematic sheet info, polished some schematic things, and made DNP parts DNP.
2026-06-22 updated symbols and started new 2771 symbol
2026-06-23 Routine push
    Began update to GPS chip
2026-06-24 Routine push
    Reference schematic pasted for MAX2769
2026-06-24 Routine Push
    Andrew should look at the MAX2769 change.
2026-06-25 Routine Push
    Various small changes made
2026-06-26 Routine Push
    First attempt to clean up schematic
2026-06-27 Routine Push
    Schematic finished. Components laid out, chasing ERCs.
2026-06-28 Routine Push
2026-06-29 Push for Layout review
2026-06-29 Cleaned up silkscreen
2026-06-29 General cleanup of schematic and layout
    Updated .gitignore, updates DRU file, moved RF lines to RF-50-MIN (max is just too big),
    lots of cleanup on the root page to make it pretty, cleaned up some redudant labels,
    updated SMPM connector and added rule zone, updated PCB outline to include NPTH drills
    for SMPM connectors, began cleanup of OPD.
2026-06-29 Set up makefile for build
2026-06-30 Minor layout changes
